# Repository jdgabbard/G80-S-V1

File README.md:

# G80-S V1
 G80-S v1.0 SBC

The G80-S Micro SBC.  The first computer I designed, and what led to many projects afterwards.  This computer has been the basis for many other computers that I have designed over the years.  And after quite a bit of consideration, I have decided to open source the design files for the world to use/abuse.

The source code for the firmware can be found here: https://github.com/jdgabbard/z80-G-DOS

Or, you can download one of the previous versions from my website's download page: http://retrodepot.net/?page_id=510

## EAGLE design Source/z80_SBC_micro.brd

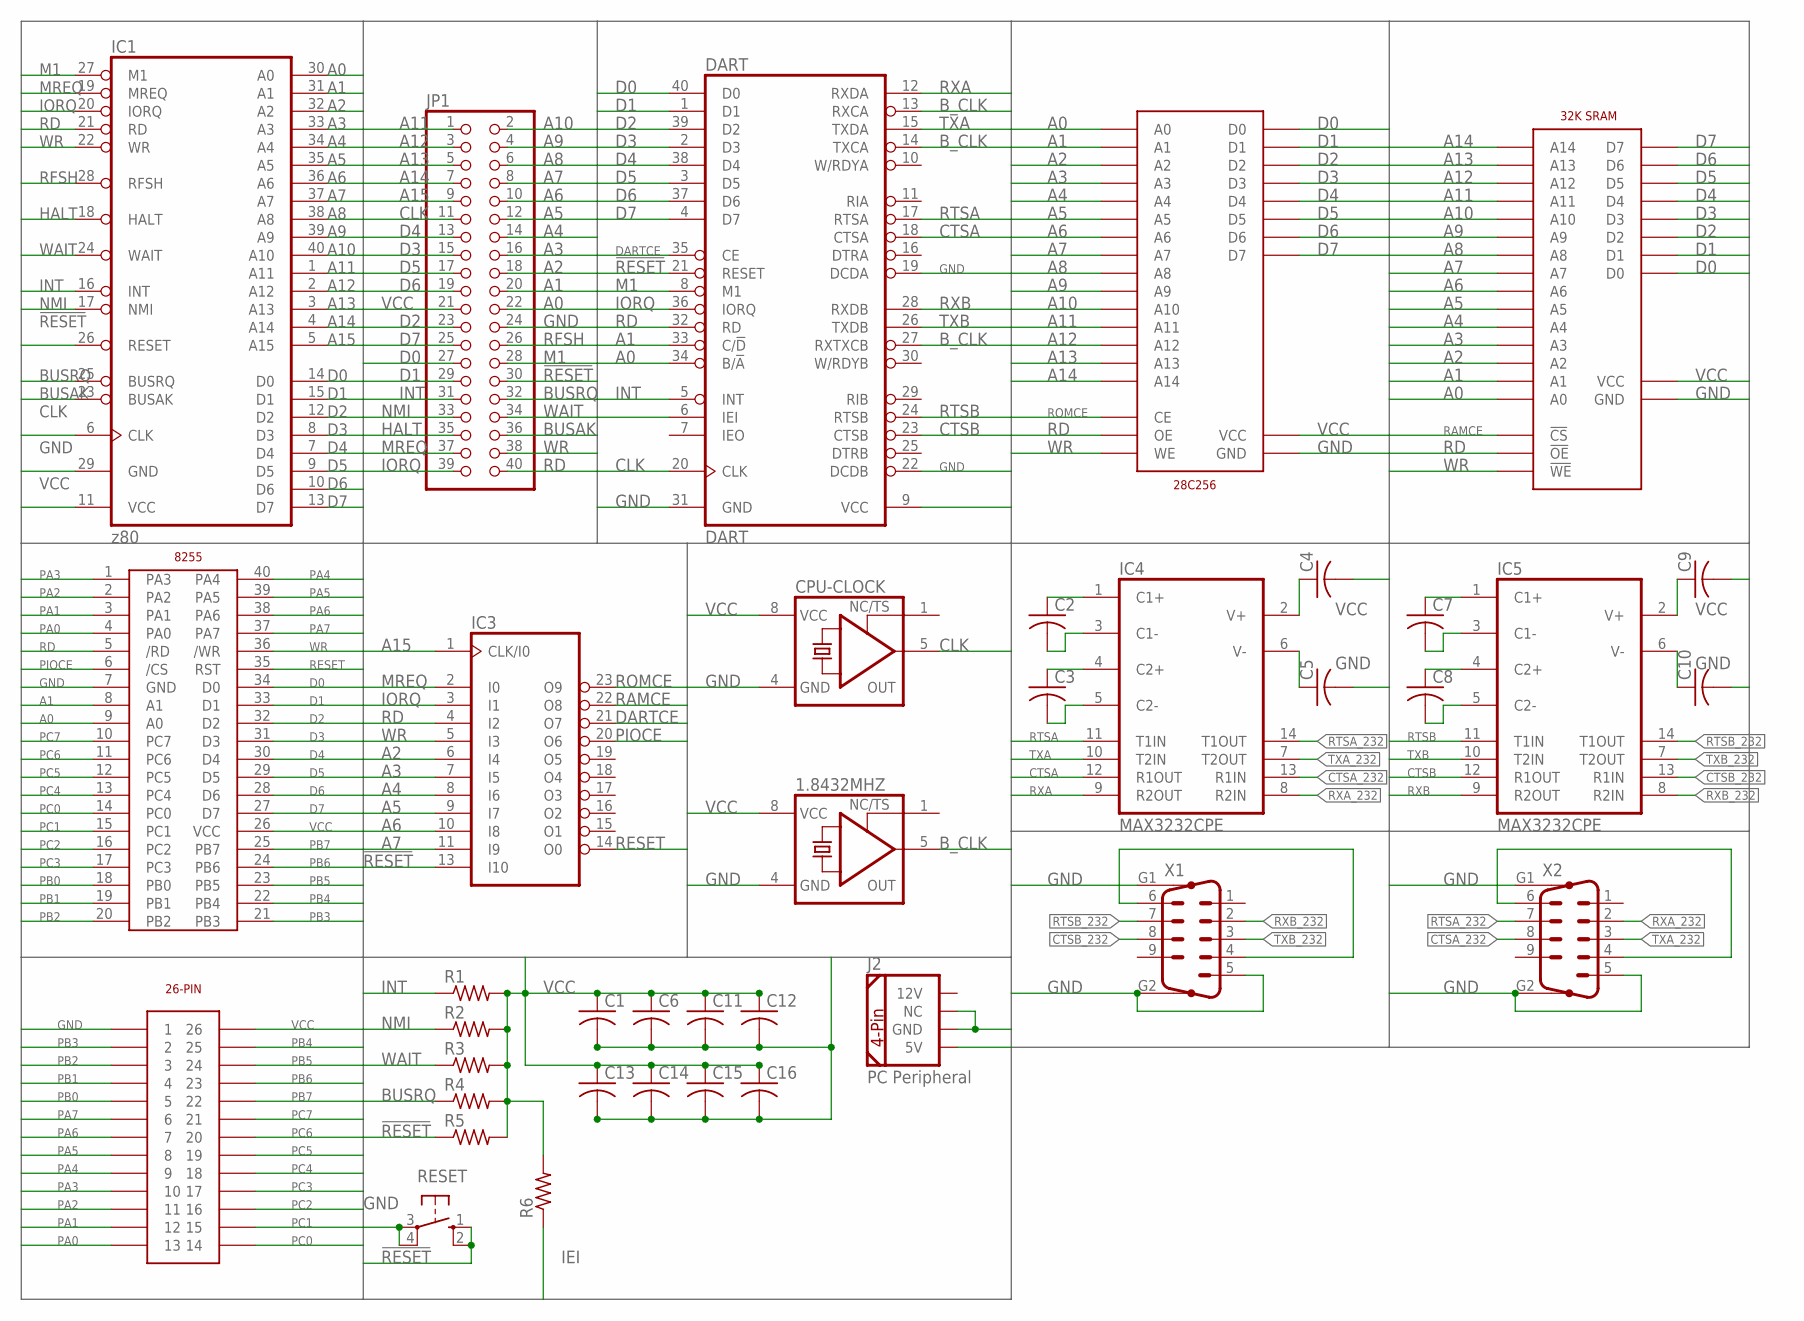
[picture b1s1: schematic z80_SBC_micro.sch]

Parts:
1.8432MHZ: XO-8; DIL08S
28C256: 28C256; DIP28
C1, C2, C3, C4, C5, C6, C7, C8, C9, C10, C11, C12, C13, C14, C15, C16: C-USC0805; C0805
CPU-CLOCK: XO-8; DIL08S
DART: DART; DIL40
IC1: z80; DIL40
IC3: 22V10; DIL24-3
IC4, IC5: MAX3232CPE; DIL16
J1: SOCKET-DIP26
J2: PC Peripheral; COMPUTER-PERIPHERAL-POWER
JP1: PINHD-2X20; 2X20
R1, R2, R3, R4, R5, R6: R-US_M0805; M0805
RESET: 10-XX; B3F-10XX
U1: 32K SRAM; DIP28-300
U$1: 8255
X1, X2: M09HP

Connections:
!RESET: DART.21 (RESET), IC1.26 (RESET), IC3.13 (I10), JP1.30, R5.1, RESET.1 (S), RESET.2 (S1)
A0: 28C256.P$10 (A0), DART.34 (B/!A), IC1.30 (A0), JP1.22, U1.P$10 (A0), U$1.9 (A0)
A1: 28C256.P$9 (A1), DART.33 (C/!D), IC1.31 (A1), JP1.20, U1.P$9 (A1), U$1.8 (A1)
A2: 28C256.P$8 (A2), IC1.32 (A2), IC3.6 (I4), JP1.18, U1.P$8 (A2)
A3: 28C256.P$7 (A3), IC1.33 (A3), IC3.7 (I5), JP1.16, U1.P$7 (A3)
A4: 28C256.P$6 (A4), IC1.34 (A4), IC3.8 (I6), JP1.14, U1.P$6 (A4)
A5: 28C256.P$5 (A5), IC1.35 (A5), IC3.9 (I7), JP1.12, U1.P$5 (A5)
A6: 28C256.P$4 (A6), IC1.36 (A6), IC3.10 (I8), JP1.10, U1.P$4 (A6)
A7: 28C256.P$3 (A7), IC1.37 (A7), IC3.11 (I9), JP1.8, U1.P$3 (A7)
A8: 28C256.P$25 (A8), IC1.38 (A8), JP1.6, U1.P$25 (A8)
A9: 28C256.P$24 (A9), IC1.39 (A9), JP1.4, U1.P$24 (A9)
A10: 28C256.P$21 (A10), IC1.40 (A10), JP1.2, U1.P$21 (A10)
A11: 28C256.P$23 (A11), IC1.1 (A11), JP1.1, U1.P$23 (A11)
A12: 28C256.P$2 (A12), IC1.2 (A12), JP1.3, U1.P$2 (A12)
A13: 28C256.P$26 (A13), IC1.3 (A13), JP1.5, U1.P$26 (A13)
A14: 28C256.P$1 (A14), IC1.4 (A14), JP1.7, U1.P$1 (A14)
A15: IC1.5 (A15), IC3.1 (CLK/I0), JP1.9
BUSAK: IC1.23 (BUSAK), JP1.36
BUSRQ: IC1.25 (BUSRQ), JP1.32, R4.1
B_CLK: 1.8432MHZ.5 (OUT), DART.13 (RXCA), DART.14 (TXCA), DART.27 (RXTXCB)
CLK: CPU-CLOCK.5 (OUT), DART.20 (CLK), IC1.6 (CLK), JP1.11
CTSA: DART.18 (CTSA), IC4.12 (R1OUT)
CTSA_232: IC4.13 (R1IN), X2.8
CTSB: DART.23 (CTSB), IC5.12 (R1OUT)
CTSB_232: IC5.13 (R1IN), X1.8
D0: 28C256.P$11 (D0), DART.40 (D0), IC1.14 (D0), JP1.27, U1.P$11 (D0), U$1.34 (D0)
D1: 28C256.P$12 (D1), DART.1 (D1), IC1.15 (D1), JP1.29, U1.P$12 (D1), U$1.33 (D1)
D2: 28C256.P$13 (D2), DART.39 (D2), IC1.12 (D2), JP1.23, U1.P$13 (D2), U$1.32 (D2)
D3: 28C256.P$15 (D3), DART.2 (D3), IC1.8 (D3), JP1.15, U1.P$15 (D3), U$1.31 (D3)
D4: 28C256.P$16 (D4), DART.38 (D4), IC1.7 (D4), JP1.13, U1.P$16 (D4), U$1.30 (D4)
D5: 28C256.P$17 (D5), DART.3 (D5), IC1.9 (D5), JP1.17, U1.P$17 (D5), U$1.29 (D5)
D6: 28C256.P$18 (D6), DART.37 (D6), IC1.10 (D6), JP1.19, U1.P$18 (D6), U$1.28 (D6)
D7: 28C256.P$19 (D7), DART.4 (D7), IC1.13 (D7), JP1.25, U1.P$19 (D7), U$1.27 (D7)
DARTCE: DART.35 (CE), IC3.21 (O7)
GND: 1.8432MHZ.4 (GND), 28C256.P$14 (GND), C1.2, C5.2, C6.2, C10.2, C11.2, C12.2, C13.2, C14.2, C15.2, C16.2, CPU-CLOCK.4 (GND), DART.19 (DCDA), DART.22 (DCDB), DART.31 (GND), IC1.29 (GND), IC3.12 (GND), IC4.15 (GND), IC5.15 (GND), J1.P$1 (1), J2.GND, J2.NC, JP1.24, RESET.3, RESET.4 (P1), U1.P$14 (GND), U$1.7 (GND), X1.5, X1.G1, X1.G2, X2.5, X2.G1, X2.G2
HALT: IC1.18 (HALT), JP1.35
IEI: DART.6 (IEI), R6.1
INT: DART.5 (INT), IC1.16 (INT), JP1.31, R1.1
IORQ: DART.36 (IORQ), IC1.20 (IORQ), IC3.3 (I1), JP1.39
M1: DART.8 (M1), IC1.27 (M1), JP1.28
MREQ: IC1.19 (MREQ), IC3.2 (I0), JP1.37
unnamed: C7.1, IC5.1 (C1+)
unnamed: C8.1, IC5.4 (C2+)
unnamed: C8.2, IC5.5 (C2-)
unnamed: C7.2, IC5.3 (C1-)
unnamed: C9.1, IC5.2 (V+)
unnamed: C10.1, IC5.6 (V-)
unnamed: C2.1, IC4.1 (C1+)
unnamed: C3.1, IC4.4 (C2+)
unnamed: C2.2, IC4.3 (C1-)
unnamed: C3.2, IC4.5 (C2-)
unnamed: C4.1, IC4.2 (V+)
unnamed: C5.1, IC4.6 (V-)
unnamed: X1.4, X1.6
unnamed: X2.4, X2.6
NMI: IC1.17 (NMI), JP1.33, R2.1
PA0: J1.P$13 (13), U$1.4 (PA0)
PA1: J1.P$12 (12), U$1.3 (PA1)
PA2: J1.P$11 (11), U$1.2 (PA2)
PA3: J1.P$10 (10), U$1.1 (PA3)
PA4: J1.P$9 (9), U$1.40 (PA4)
PA5: J1.P$8 (8), U$1.39 (PA5)
PA6: J1.P$7 (7), U$1.38 (PA6)
PA7: J1.P$6 (6), U$1.37 (PA7)
PB0: J1.P$5 (5), U$1.18 (PB0)
PB1: J1.P$4 (4), U$1.19 (PB1)
PB2: J1.P$3 (3), U$1.20 (PB2)
PB3: J1.P$2 (2), U$1.21 (PB3)
PB4: J1.P$25 (25), U$1.22 (PB4)
PB5: J1.P$24 (24), U$1.23 (PB5)
PB6: J1.P$23 (23), U$1.24 (PB6)
PB7: J1.P$22 (22), U$1.25 (PB7)
PC0: J1.P$14 (14), U$1.14 (PC0)
PC1: J1.P$15 (15), U$1.15 (PC1)
PC2: J1.P$16 (16), U$1.16 (PC2)
PC3: J1.P$17 (17), U$1.17 (PC3)
PC4: J1.P$18 (18), U$1.13 (PC4)
PC5: J1.P$19 (19), U$1.12 (PC5)
PC6: J1.P$20 (20), U$1.11 (PC6)
PC7: J1.P$21 (21), U$1.10 (PC7)
PIOCE: IC3.20 (O6), U$1.6 (/CS)
RAMCE: IC3.22 (O8), U1.P$20 (!CS)
RD: 28C256.P$22 (OE), DART.32 (RD), IC1.21 (RD), IC3.4 (I2), JP1.40, U1.P$22 (!OE), U$1.5 (/RD)
RESET: IC3.14 (O0), U$1.35 (RST)
RFSH: IC1.28 (RFSH), JP1.26
ROMCE: 28C256.P$20 (CE), IC3.23 (O9)
RTSA: DART.17 (RTSA), IC4.11 (T1IN)
RTSA_232: IC4.14 (T1OUT), X2.7
RTSB: DART.24 (RTSB), IC5.11 (T1IN)
RTSB_232: IC5.14 (T1OUT), X1.7
RXA: DART.12 (RXDA), IC4.9 (R2OUT)
RXA_232: IC4.8 (R2IN), X2.2
RXB: DART.28 (RXDB), IC5.9 (R2OUT)
RXB_232: IC5.8 (R2IN), X1.2
TXA: DART.15 (TXDA), IC4.10 (T2IN)
TXA_232: IC4.7 (T2OUT), X2.3
TXB: DART.26 (TXDB), IC5.10 (T2IN)
TXB_232: IC5.7 (T2OUT), X1.3
VCC: 1.8432MHZ.8 (VCC), 28C256.P$28 (VCC), C1.1, C4.2, C6.1, C9.2, C11.1, C12.1, C13.1, C14.1, C15.1, C16.1, CPU-CLOCK.8 (VCC), DART.9 (VCC), IC1.11 (VCC), IC3.24 (VCC), IC4.16 (VCC), IC5.16 (VCC), J1.P$26 (26), J2.5V, JP1.21, R1.2, R2.2, R3.2, R4.2, R5.2, R6.2, U1.P$28 (VCC), U$1.26 (VCC)
WAIT: IC1.24 (WAIT), JP1.34, R3.1
WR: 28C256.P$27 (WE), IC1.22 (WR), IC3.5 (I3), JP1.38, U1.P$27 (!WE), U$1.36 (/WR)

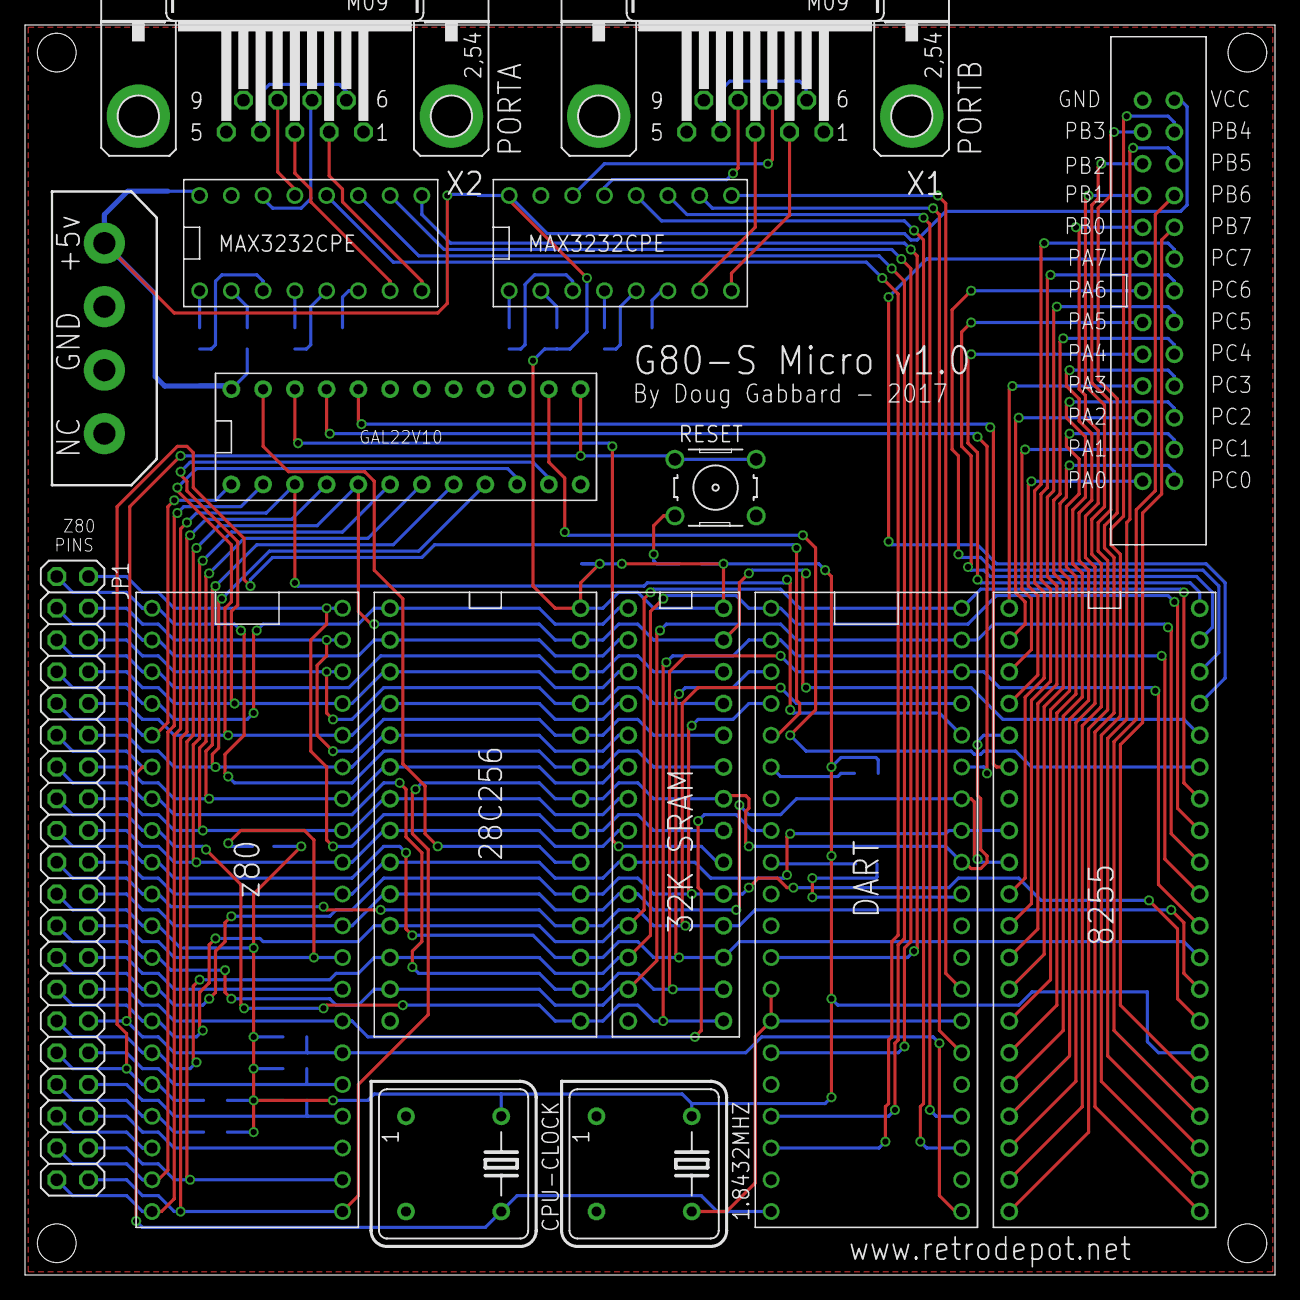
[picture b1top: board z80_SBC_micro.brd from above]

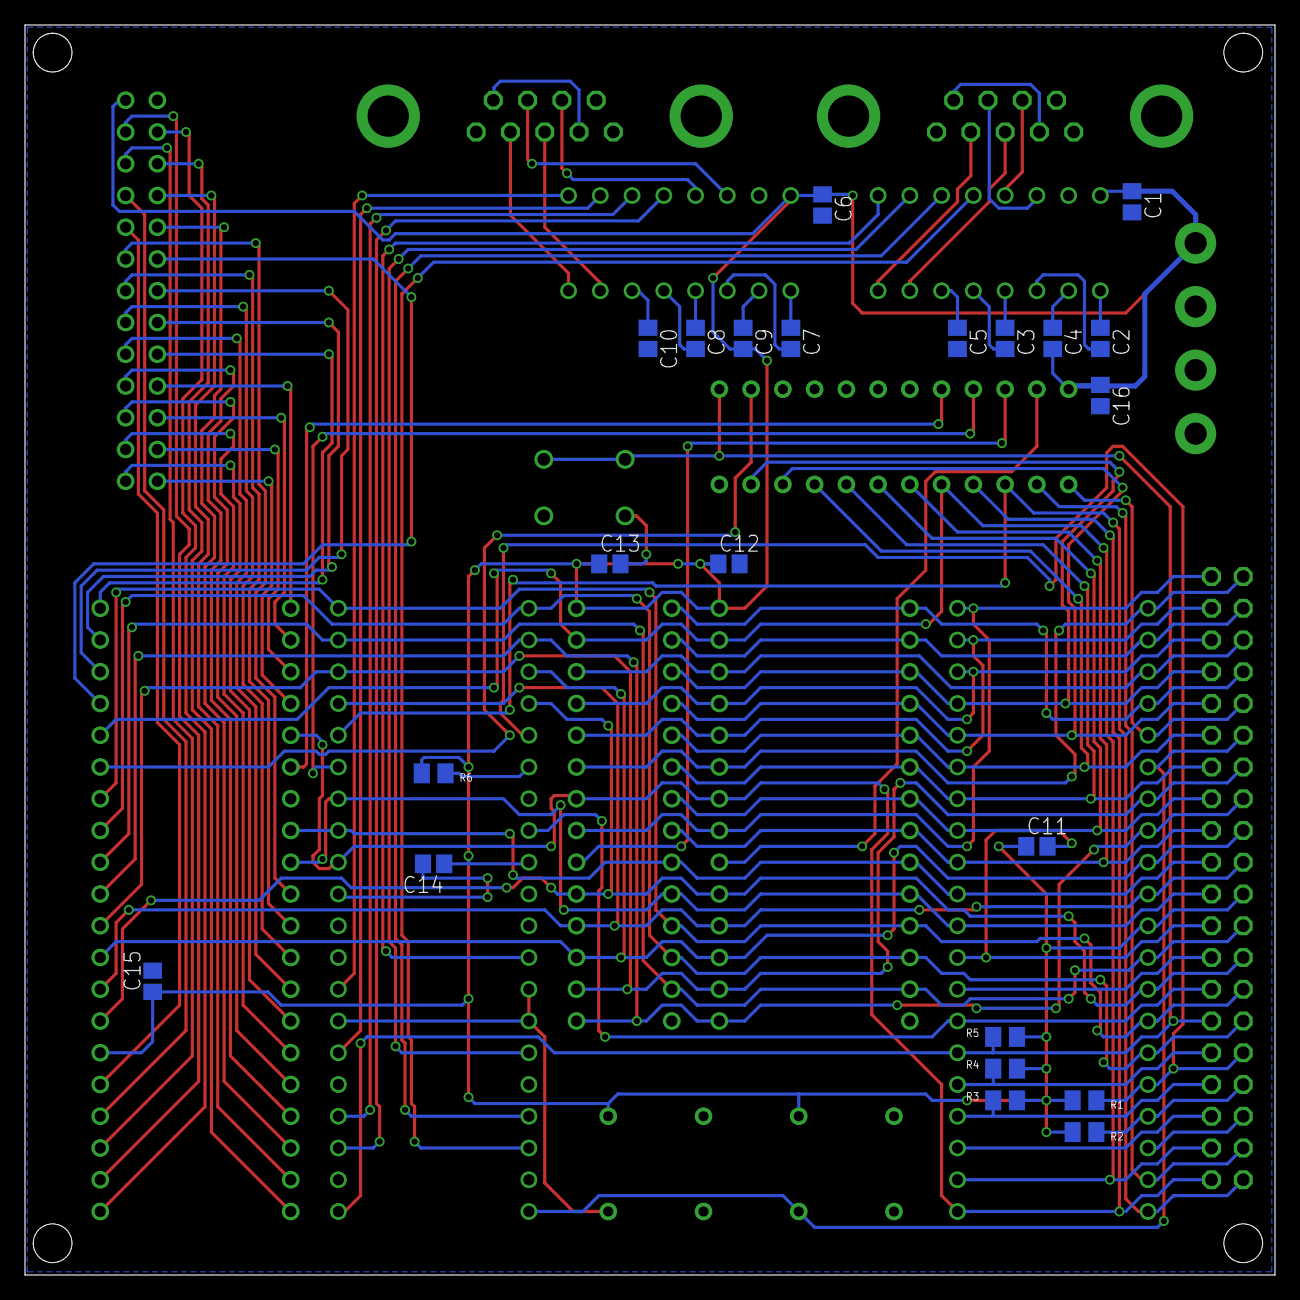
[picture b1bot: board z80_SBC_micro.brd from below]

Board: 2 copper layers, 100.0 x 100.0 mm, 38 parts (22 on the bottom side), 101 nets.

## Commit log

2022-02-26 Initial Upload

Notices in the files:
parts and their libraries:
SparkFun-Connectors: Licensing: Creative Commons ShareAlike 4.0 International - https://creativecommons.org/licenses/by-sa/4.0
